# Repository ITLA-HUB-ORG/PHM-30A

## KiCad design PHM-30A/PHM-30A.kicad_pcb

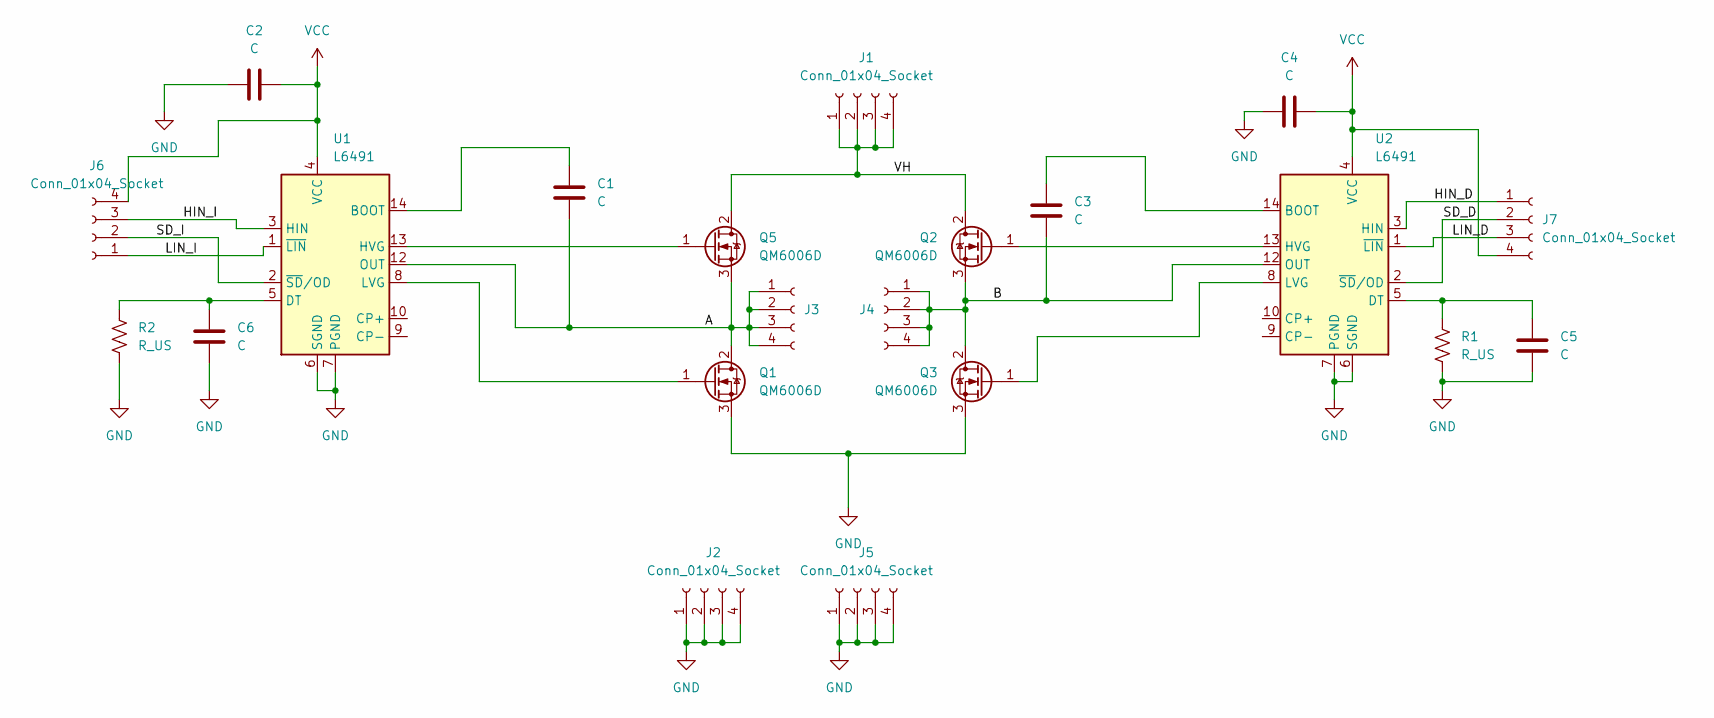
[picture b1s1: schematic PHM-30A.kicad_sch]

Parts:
C1, C2, C3, C4: C; C_0805_2012Metric
C5, C6: C; C_0603_1608Metric
J1, J2, J3, J4, J5, J6, J7: Conn_01x04_Socket; PinSocket_1x04_P1.27mm_Castellated
Q1, Q2, Q3, Q5: QM6006D; TO-252-2
R1, R2: R_US; R_0603_1608Metric
U1, U2: L6491; SO-14_3.9x8.65mm_P1.27mm

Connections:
/A: C1.2, J3.1, J3.2, J3.3, J3.4, Q1.2 (D), Q5.3 (S), U1.12 (OUT)
/B: C3.2, J4.1, J4.2, J4.3, J4.4, Q2.3 (S), Q3.2 (D), U2.12 (OUT)
/HIN_D: J7.1, U2.3 (HIN)
/HIN_I: J6.3, U1.3 (HIN)
/LIN_D: J7.3, U2.1 (~LIN)
/LIN_I: J6.1, U1.1 (~LIN)
/SD_D: J7.2, U2.2 (~SD/OD)
/SD_I: J6.2, U1.2 (~SD/OD)
/VH: J1.1, J1.2, J1.3, J1.4, Q2.2 (D), Q5.2 (D)
GND: C2.2, C4.1, C5.1, C6.1, J2.1, J2.2, J2.3, J2.4, J5.1, J5.2, J5.3, J5.4, Q1.3 (S), Q3.3 (S), R1.2, R2.2, U1.6 (SGND), U1.7 (PGND), U2.6 (SGND), U2.7 (PGND)
unnamed: Q1.1 (G), U1.8 (LVG)
unnamed: Q2.1 (G), U2.13 (HVG)
unnamed: Q3.1 (G), U2.8 (LVG)
unnamed: Q5.1 (G), U1.13 (HVG)
unnamed: C1.1, U1.14 (BOOT)
unnamed: C6.2, R2.1, U1.5 (DT)
unnamed: C3.1, U2.14 (BOOT)
unnamed: C5.2, R1.1, U2.5 (DT)
VCC: C2.1, C4.2, J6.4, J7.4, U1.4 (VCC), U2.4 (VCC)

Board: 2 copper layers, 21 parts (0 on the bottom side), 19 nets, no tracks yet.

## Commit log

2026-03-02 Modificado el part number de D1 y D2 Modificado el Footprint del Gyroscopio para marcar el pin 1 en el silkscreen
